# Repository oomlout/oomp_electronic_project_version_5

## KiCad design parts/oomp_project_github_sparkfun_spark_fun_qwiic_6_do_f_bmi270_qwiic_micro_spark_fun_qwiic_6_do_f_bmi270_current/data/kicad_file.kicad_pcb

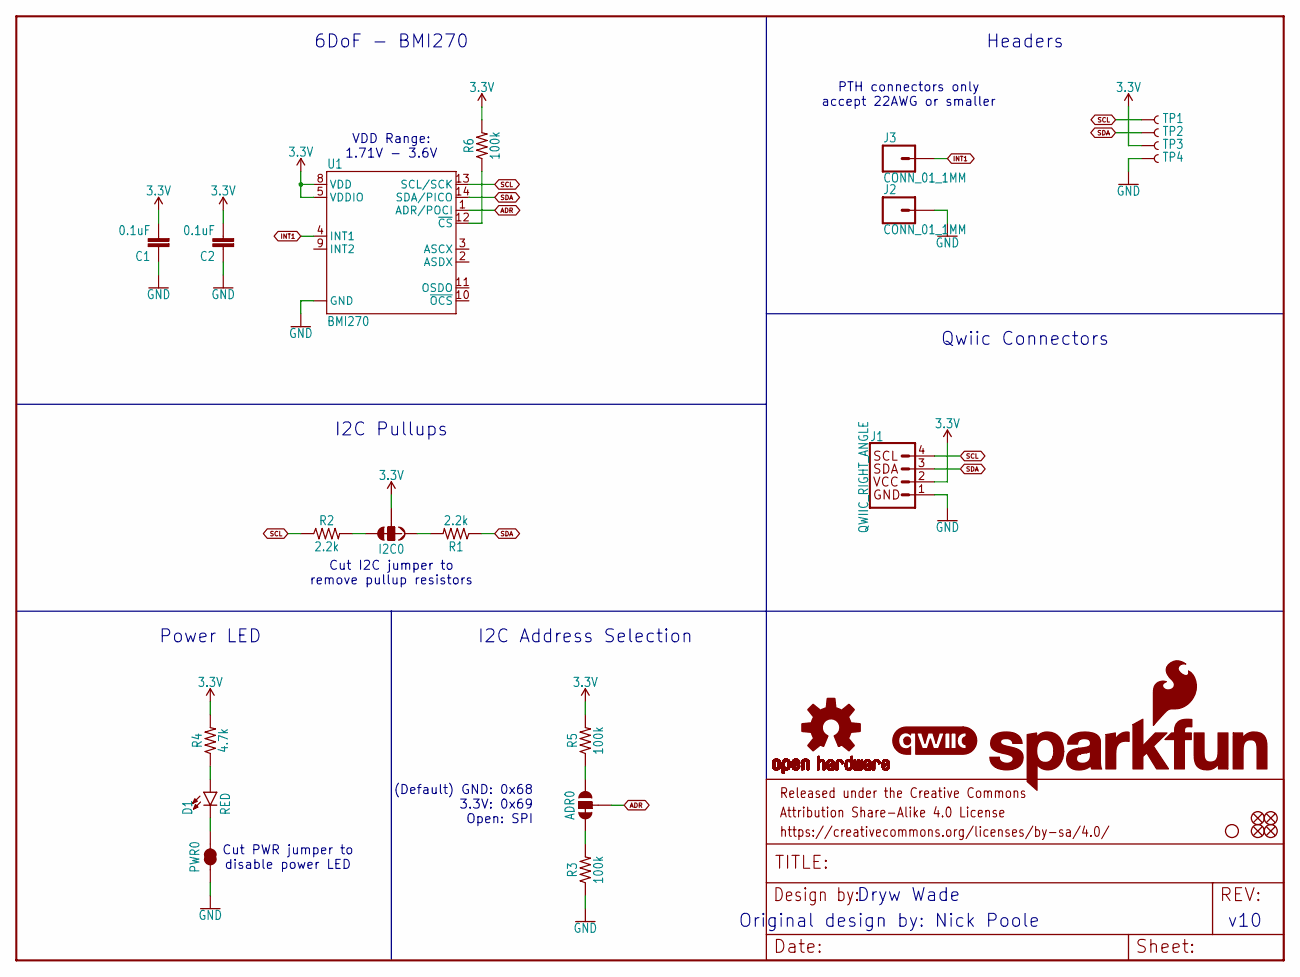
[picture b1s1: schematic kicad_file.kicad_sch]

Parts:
ADR0: JUMPER-SMT_3_1-NC_TRACE_SILK; SMT-JUMPER_3_1-NC_TRACE_SILK
C1, C2: 0.1uF; 0402-TIGHT
D1: RED; LED-0402
FD1, FD2, FD3, FD4: FIDUCIALUFIDUCIAL; FIDUCIAL-MICRO
FRAME1: FRAME-LETTER; CREATIVE_COMMONS
H1: STAND-OFF
I2C0: JUMPER-SMT_3_2-NC_TRACE_SILK; SMT-JUMPER_3_2-NC_TRACE_SILK
J1: QWIIC_RIGHT_ANGLE; JST04_1MM_RA
J2, J3: CONN_01_1MM; 1X01_1MM_NO_SILK
LOGO1: SFE_LOGO_NAME_FLAMEBLANK; BLANK
LOGO2: QWIIC_LOGO_3MM; QWIIC_3MM
LOGO3: OSHW-LOGOMINI; OSHW-LOGO-MINI
PWR0: JUMPER-SMT_2_NC_TRACE_SILK; SMT-JUMPER_2_NC_TRACE_SILK
R1, R2: 2.2k; 0402-TIGHT
R3, R5, R6: 100k; 0402-TIGHT
R4: 4.7k; 0402-TIGHT
TP1, TP2, TP3, TP4: TEST-POINT3; PAD.03X.03
U1: BMI270

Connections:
3.3V: C1.2, C2.2, I2C0.2, J1.2, R4.2, R5.2, R6.2, TP3.1, U1.5 (VDDIO), U1.8 (VDD)
ADR: ADR0.2, U1.1 (ADR/POCI)
GND: C1.1, C2.1, J1.1, J2.1, PWR0.1, R3.1, TP4.1, U1.6 (GND), U1.7 (GND)
INT1: J3.1, U1.4 (INT1)
unnamed: I2C0.1, R1.2
unnamed: I2C0.3, R2.2
unnamed: D1.C, PWR0.2
unnamed: D1.A, R4.1
unnamed: ADR0.1, R5.1
unnamed: ADR0.3, R3.2
unnamed: R6.1, U1.12 (~CS)
SCL: J1.4, R2.1, TP1.1, U1.13 (SCL/SCK)
SDA: J1.3, R1.1, TP2.1, U1.14 (SDA/PICO)

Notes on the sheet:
Qwiic Connectors
Power LED
I2C Pullups
Dryw Wade
v10
Original design by: Nick Poole
Cut I2C jumper to remove pullup resistors
Cut PWR jumper to disable power LED
6DoF - BMI270
I2C Address Selection
Headers
PTH connectors only accept 22AWG or smaller
VDD Range: 1.71V - 3.6V
(Default) GND: 0x68 3.3V: 0x69 Open: SPI

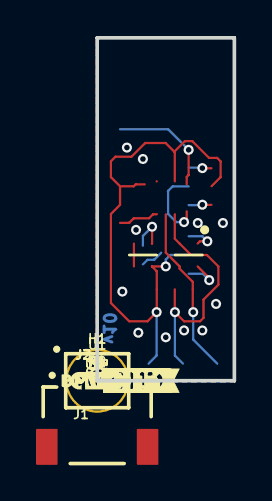
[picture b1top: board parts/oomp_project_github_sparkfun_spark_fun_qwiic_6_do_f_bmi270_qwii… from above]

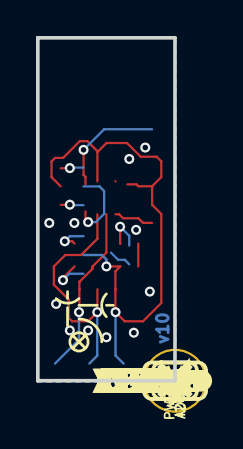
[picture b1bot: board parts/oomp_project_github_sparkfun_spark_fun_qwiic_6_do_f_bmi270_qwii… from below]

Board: 2 copper layers, 7.6 x 19.1 mm, 45 parts (22 on the bottom side), 13 nets.

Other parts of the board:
U$1: #I2C#0
U$2, U$7: #GND#0
U$3: SFE_LOGO_FLAME_.1
U$4: #PWR#0
U$5: #ADR#0
U$6: #0X68#0
U$8, U$9: #INT1#0
U$18: #0X69#0
U$21: BMI2700
U$33: ORDERING_INSTRUCTIONS
U$34: PWR0
U$79: X0
U$80: Y0
U$81: Z0

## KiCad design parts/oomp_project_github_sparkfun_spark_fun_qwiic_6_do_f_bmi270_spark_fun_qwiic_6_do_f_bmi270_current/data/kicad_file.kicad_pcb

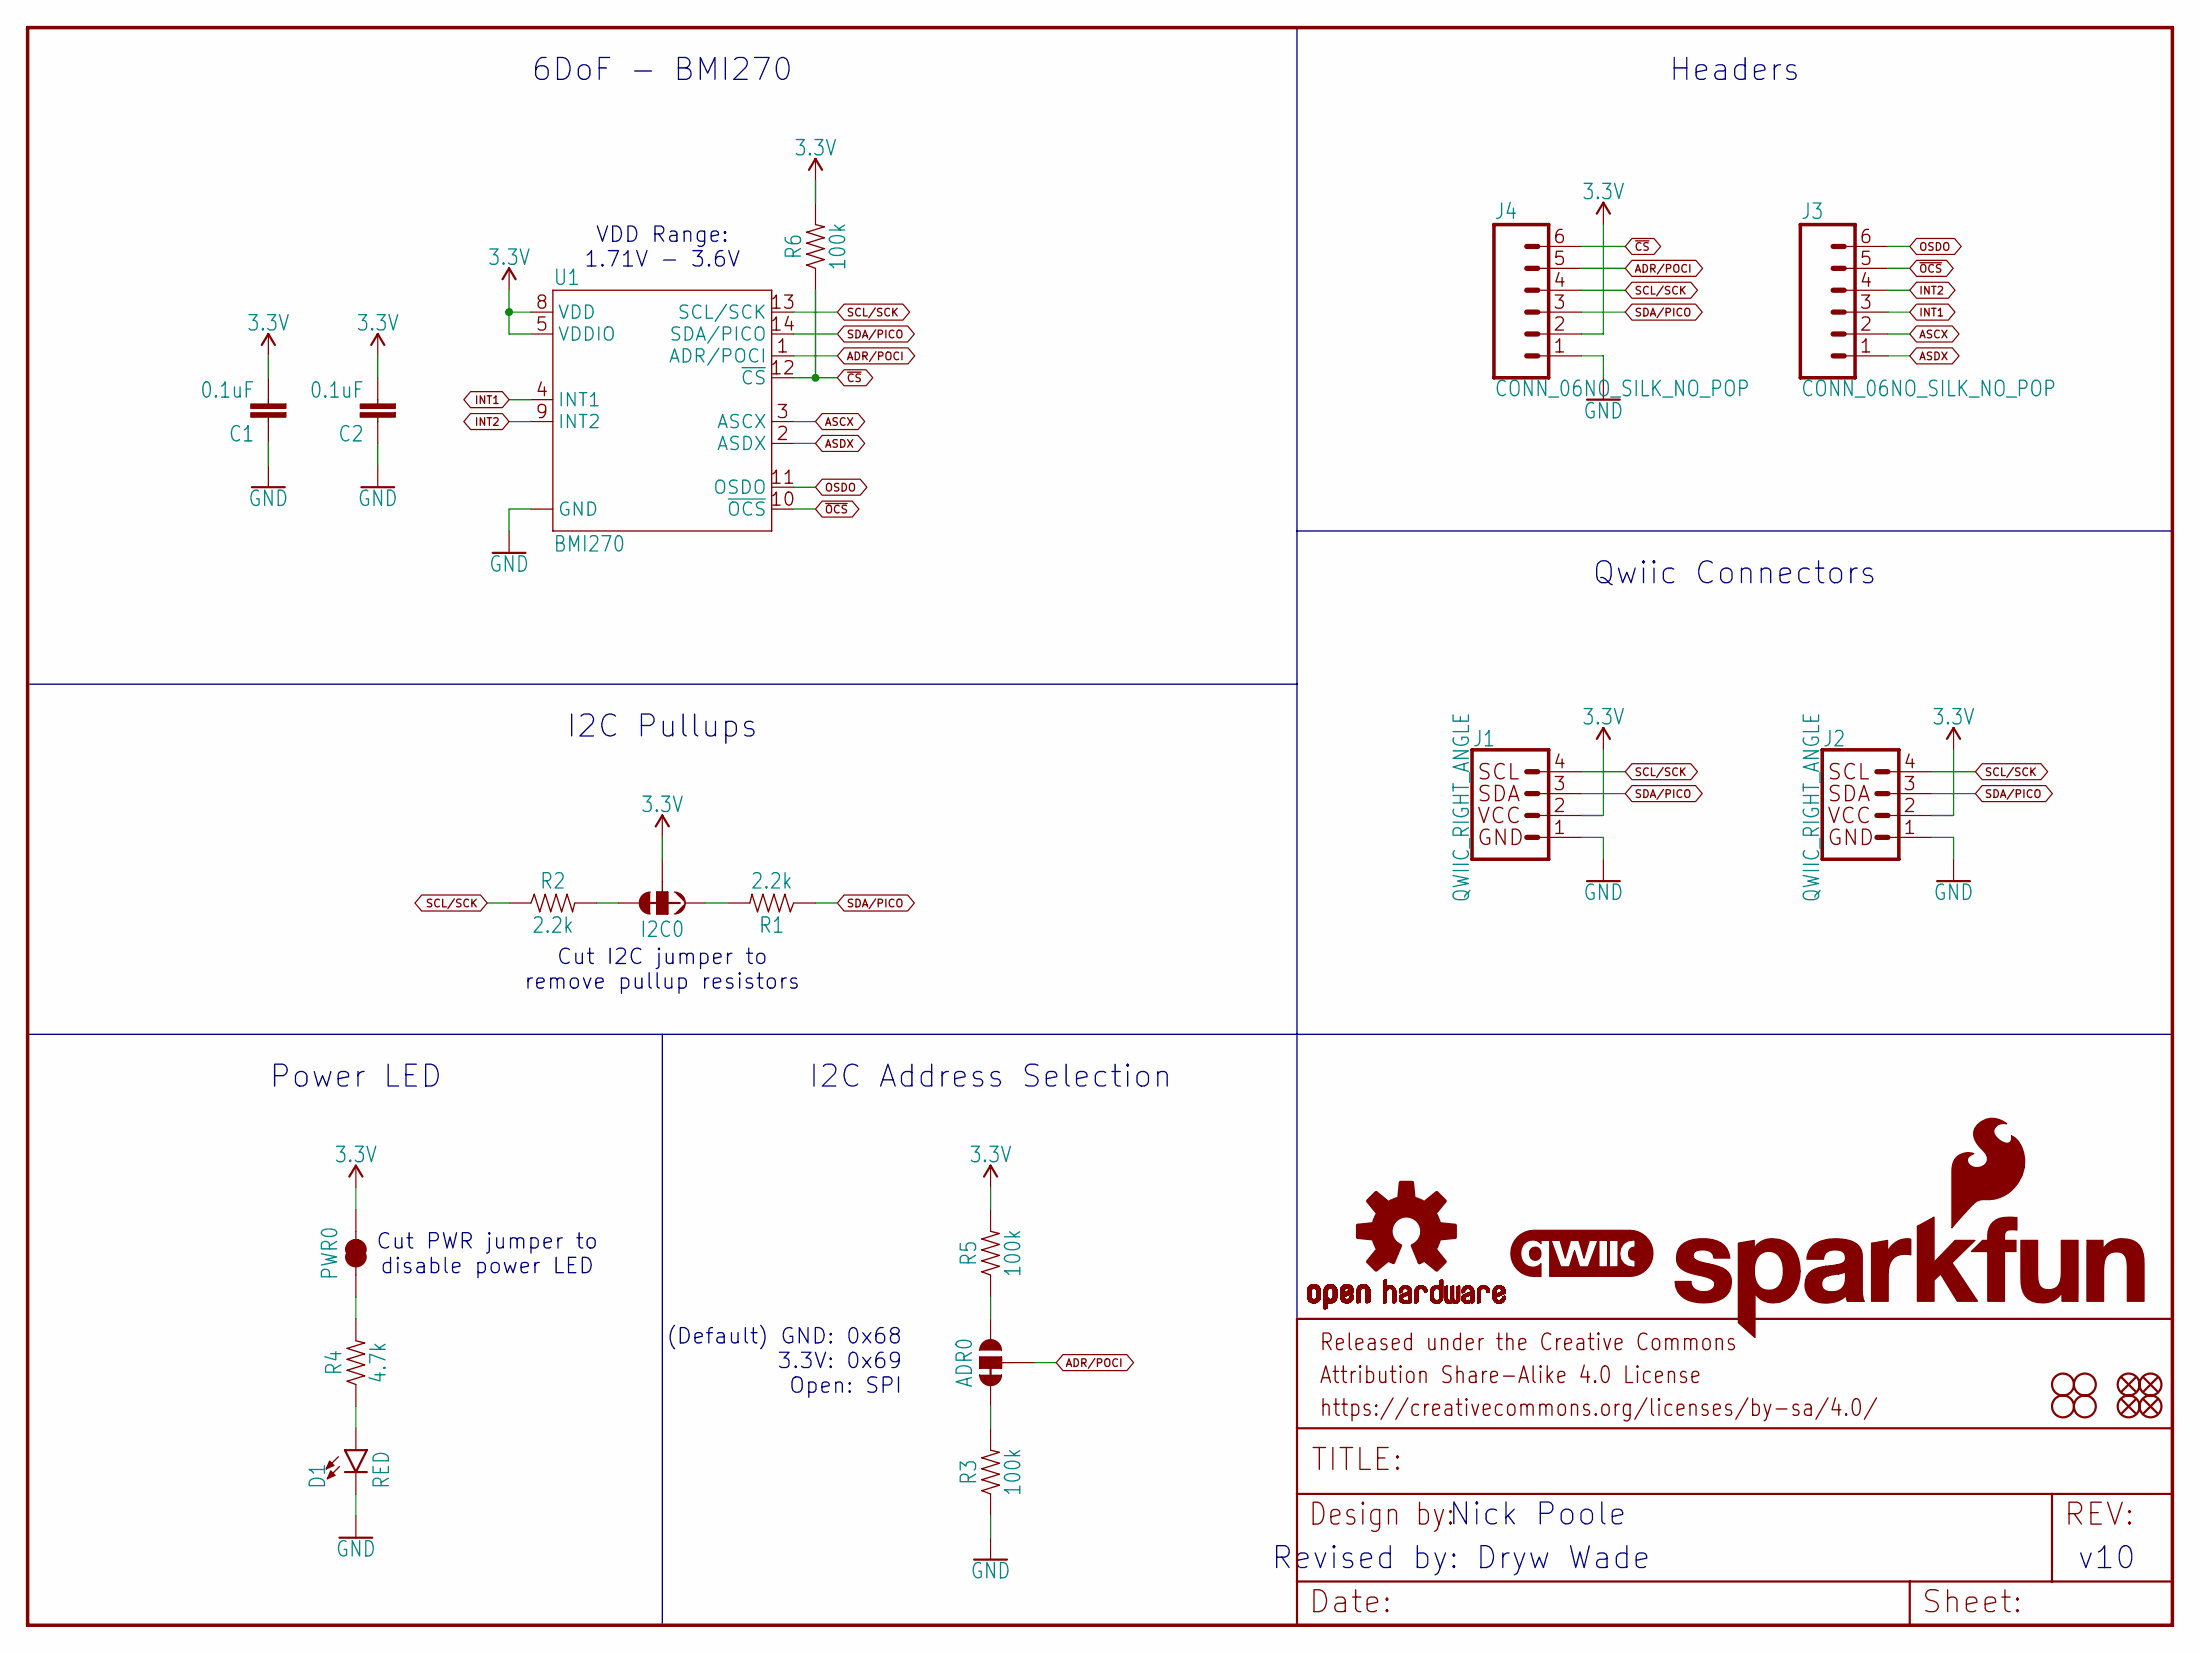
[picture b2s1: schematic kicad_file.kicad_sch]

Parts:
ADR0: JUMPER-SMT_3_1-NC_TRACE_SILK; SMT-JUMPER_3_1-NC_TRACE_SILK
C1, C2: 0.1uF; 0603
D1: RED; LED-0603
FD1, FD2, FD3, FD4: FIDUCIAL1X2; FIDUCIAL-1X2
FRAME1: FRAME-LETTER; CREATIVE_COMMONS
H1, H2, H3, H4: STAND-OFF
I2C0: JUMPER-SMT_3_2-NC_TRACE_SILK; SMT-JUMPER_3_2-NC_TRACE_SILK
J1, J2: QWIIC_RIGHT_ANGLE; JST04_1MM_RA
J3, J4: CONN_06NO_SILK_NO_POP; 1X06_NO_SILK
LOGO1: SFE_LOGO_NAME_FLAME.1_INCH; SFE_LOGO_NAME_FLAME_.1
LOGO2: QWIIC_LOGO_5MM; QWIIC_5MM
LOGO3: OSHW-LOGOS; OSHW-LOGO-S
PWR0: JUMPER-SMT_2_NC_TRACE_SILK; SMT-JUMPER_2_NC_TRACE_SILK
R1, R2: 2.2k; 0603
R3, R5, R6: 100k; 0603
R4: 4.7k; 0603
U1: BMI270

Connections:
3.3V: C1.2, C2.2, I2C0.2, J1.2, J2.2, J4.2, PWR0.2, R5.2, R6.2, U1.5 (VDDIO), U1.8 (VDD)
ADR/POCI: ADR0.2, J4.5, U1.1 (ADR/POCI)
ASCX: J3.2, U1.3 (ASCX)
ASDX: J3.1, U1.2 (ASDX)
GND: C1.1, C2.1, D1.C, J1.1, J2.1, J4.1, R3.1, U1.6 (GND), U1.7 (GND)
INT1: J3.3, U1.4 (INT1)
INT2: J3.4, U1.9 (INT2)
unnamed: I2C0.1, R1.2
unnamed: I2C0.3, R2.2
unnamed: PWR0.1, R4.2
unnamed: D1.A, R4.1
unnamed: ADR0.1, R5.1
unnamed: ADR0.3, R3.2
OSDO: J3.6, U1.11 (OSDO)
SCL/SCK: J1.4, J2.4, J4.4, R2.1, U1.13 (SCL/SCK)
SDA/PICO: J1.3, J2.3, J4.3, R1.1, U1.14 (SDA/PICO)
~CS: J4.6, R6.1, U1.12 (~CS)
~OCS: J3.5, U1.10 (~OCS)

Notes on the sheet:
Headers
(Default) GND: 0x68 3.3V: 0x69 Open: SPI
Revised by: Dryw Wade
v10
I2C Address Selection
VDD Range: 1.71V - 3.6V
I2C Pullups
Qwiic Connectors
Cut PWR jumper to disable power LED
Nick Poole
Cut I2C jumper to remove pullup resistors
6DoF - BMI270
Power LED

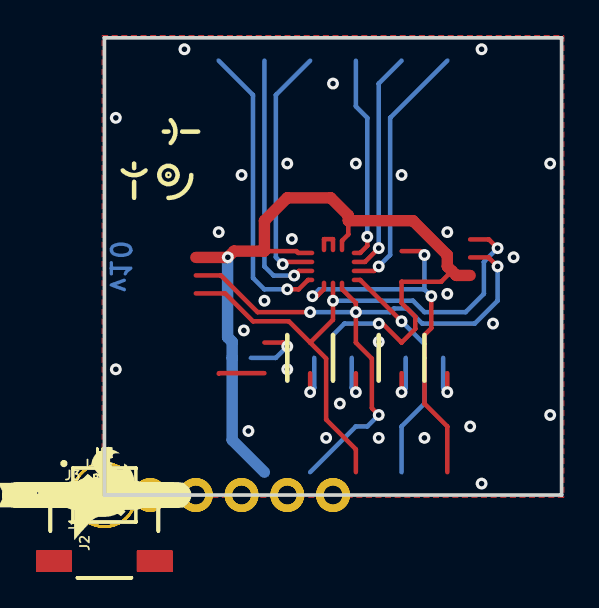
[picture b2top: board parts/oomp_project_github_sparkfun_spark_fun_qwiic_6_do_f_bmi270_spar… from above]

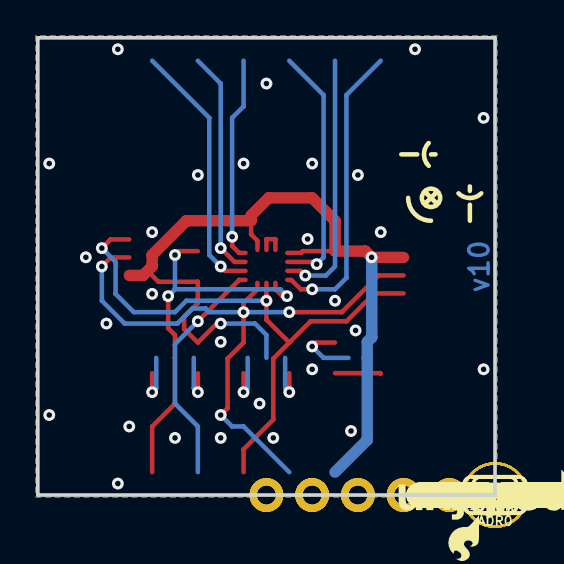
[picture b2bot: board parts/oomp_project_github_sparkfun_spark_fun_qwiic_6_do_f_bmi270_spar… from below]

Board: 2 copper layers, 25.4 x 25.4 mm, 69 parts (27 on the bottom side), 18 nets.

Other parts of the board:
U$1: #I2C#0
U$2, U$14: #_SDA#0
U$3: SFE_LOGO_FLAME_.2
U$4: #PWR#0
U$5: #ADR#0
U$6: #0X68#0
U$7, U$13: #_3V3#0
U$8, U$17: #_#CS##0
U$9, U$16: #_ADR#0
U$10, U$15: #_SCL#0
U$11, U$27: #ASDX_#0
U$12, U$19: #_GND#0
U$18: #0X69#0
U$20, U$21: BMI2700
U$22, U$28: #ASCX_#0
U$23, U$29: #INT1_#0
U$24, U$30: #INT2_#0
U$25, U$31: ##OCS#_#0
U$26, U$32: #OSDO_#0
U$33: ORDERING_INSTRUCTIONS
U$34: PWR0
U$79, U$88: X0
U$80, U$89: Y0
U$81, U$90: Z0

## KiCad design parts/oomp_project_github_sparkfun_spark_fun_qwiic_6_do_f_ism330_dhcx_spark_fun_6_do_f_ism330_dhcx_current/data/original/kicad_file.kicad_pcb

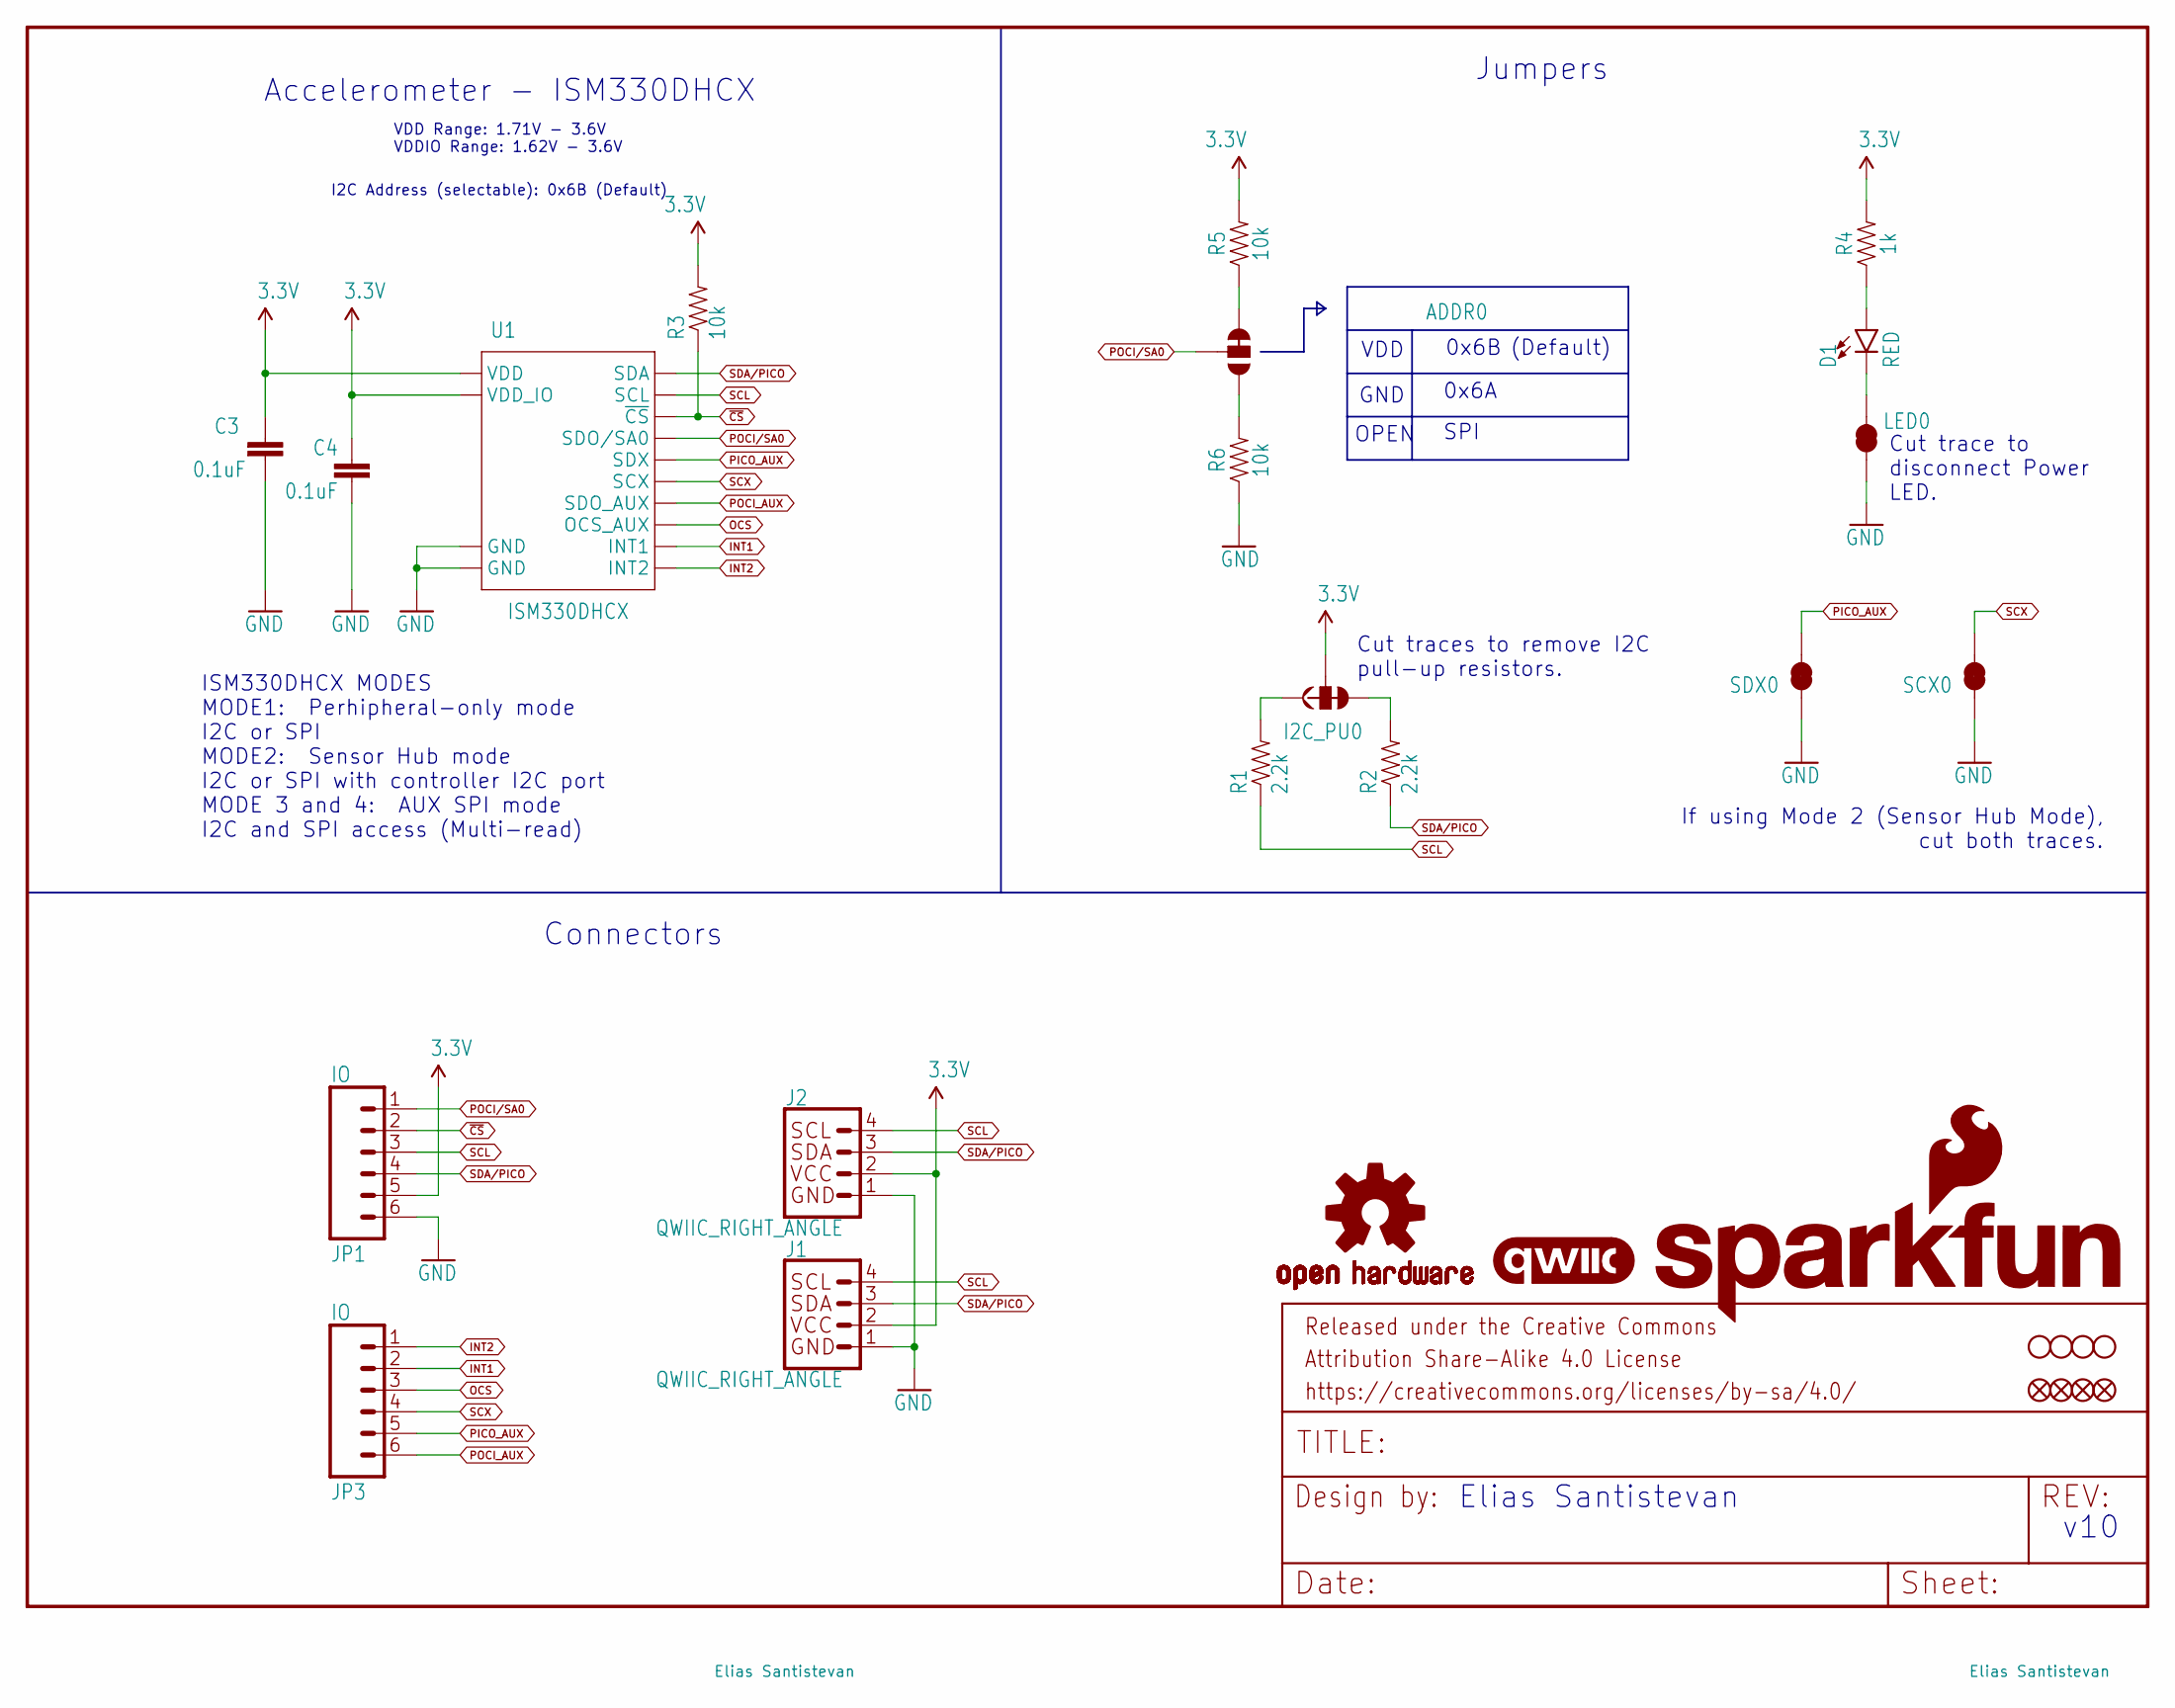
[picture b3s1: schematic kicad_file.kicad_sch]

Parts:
ADDR0: JUMPER-SMT_3_1-NC_TRACE_SILK; SMT-JUMPER_3_1-NC_TRACE_SILK
C3, C4: 0.1uF; 0603
D1: RED; LED-0603
FD1, FD2: FIDUCIALUFIDUCIAL; FIDUCIAL-MICRO
FID1, FID2: FIDUCIALUFIDUCIAL; FIDUCIAL-MICRO
FRAME1: FRAME-LETTER; CREATIVE_COMMONS
I2C_PU0: S_MODE; SMT-JUMPER_3_2-NC_TRACE_SILK
J1, J2: QWIIC_RIGHT_ANGLE; JST04_1MM_RA
JP1, JP3: IO; 1X06_NO_SILK
LED0: JUMPER-SMT_2_NC_TRACE_SILK; SMT-JUMPER_2_NC_TRACE_SILK
LOGO1: QWIIC_LOGO_4MM; QWIIC_4MM
LOGO2: OSHW-LOGOMINI; OSHW-LOGO-MINI
LOGO3: SFE_LOGO_NAME_FLAME.1_INCH; SFE_LOGO_NAME_FLAME_.1
R1, R2: 2.2k; 0603
R3, R5, R6: 10k; 0603
R4: 1k; 0603
SCX0: JUMPER-SMT_2_NC_TRACE_SILK; SMT-JUMPER_2_NC_TRACE_SILK
SDX0: JUMPER-SMT_2_NC_TRACE_SILK; SMT-JUMPER_2_NC_TRACE_SILK
STANDOFF1, STANDOFF2, STANDOFF3, STANDOFF4: STAND-OFFTIGHT; STAND-OFF-TIGHT
U1: ISM330DHCX; LGA-14L

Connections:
3.3V: C3.1, C4.1, I2C_PU0.2, J1.2, J2.2, JP1.5, R3.2, R4.2, R5.2, U1.P5 (VDD_IO), U1.P8 (VDD)
GND: C3.2, C4.2, J1.1, J2.1, JP1.6, LED0.1, R6.1, SCX0.1, SDX0.1, U1.P6 (GND), U1.P7 (GND)
INT1: JP3.2, U1.P4 (INT1)
INT2: JP3.1, U1.P9 (INT2)
unnamed: ADDR0.3, R5.1
unnamed: D1.A, R4.1
unnamed: D1.C, LED0.2
unnamed: I2C_PU0.1, R1.2
unnamed: I2C_PU0.3, R2.2
unnamed: ADDR0.1, R6.2
OCS: JP3.3, U1.P10 (OCS_AUX)
PICO_AUX: JP3.5, SDX0.2, U1.P2 (SDX)
POCI/SA0: ADDR0.2, JP1.1, U1.P1 (SDO/SA0)
POCI_AUX: JP3.6, U1.P11 (SDO_AUX)
SCL: J1.4, J2.4, JP1.3, R1.1, U1.P13 (SCL)
SCX: JP3.4, SCX0.2, U1.P3 (SCX)
SDA/PICO: J1.3, J2.3, JP1.4, R2.1, U1.P14 (SDA)
~CS: JP1.2, R3.1, U1.P12 (~CS)

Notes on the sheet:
I2C Address (selectable): 0x6B (Default)
SPI
Jumpers
Cut trace to disconnect Power LED.
0x6B
If using Mode 2 (Sensor Hub Mode), cut both traces.
Accelerometer - ISM330DHCX
GND
Connectors
Elias Santistevan
0x6A
Cut traces to remove I2C pull-up resistors.
VDD Range: 1.71V - 3.6V VDDIO Range: 1.62V - 3.6V
VDD
OPEN
v10
ISM330DHCX MODES MODE1: Perhipheral-only mode I2C or SPI MODE2: Sensor Hub mode I2C or SPI with controller I2C port MODE 3 and 4: AUX SPI mode I2C and SPI access (Multi-read)
(Default)

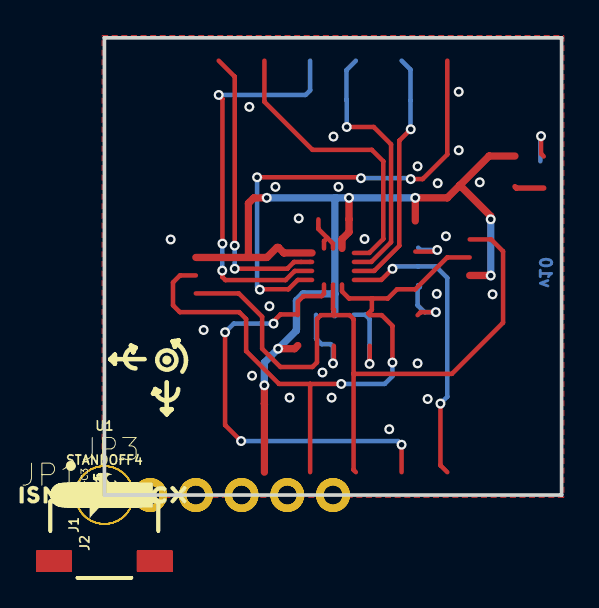
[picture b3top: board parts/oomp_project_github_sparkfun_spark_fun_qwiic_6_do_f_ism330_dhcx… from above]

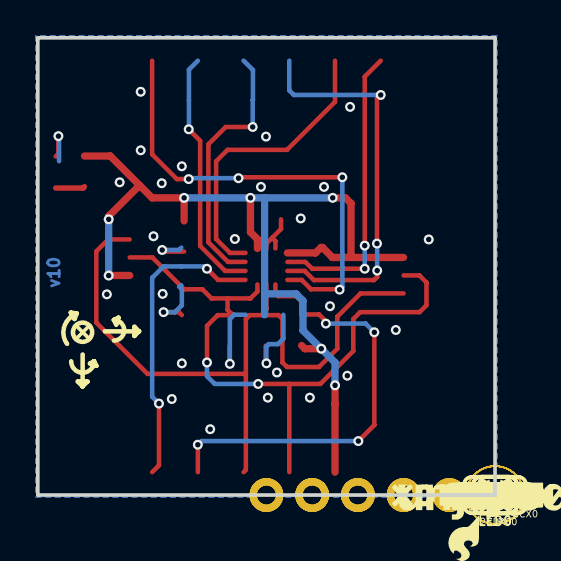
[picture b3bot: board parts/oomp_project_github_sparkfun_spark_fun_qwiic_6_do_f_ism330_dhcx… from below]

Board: 2 copper layers, 25.4 x 25.4 mm, 70 parts (30 on the bottom side), 18 nets.

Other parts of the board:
U$1, U$15: #3V3#1
U$2, U$17: #GND#0
U$3: ##CS##7
U$4: #SDA#4
U$5, U$22: #SCL#5
U$6: #POCI#11
U$7, U$19: #INT1#9
U$8: #INT2#2
U$9: #OCS#8
U$10: #SCX#9
U$11: #PICOX#10
U$12: ISM330DHCX331
U$13: #0X6A#11
U$14: #0X6B#11
U$16: #LED#11
U$18: #POCI#12
U$20: #OCS#7
U$23: #SCX#8
U$24: #POCIX#8
U$25: #I2C#11
U$26: #PICO#13
U$27: ##CS##8
U$28: PWR8
U$29: SFE_LOGO_FLAME_.1
U$30: ISM330DHCX20
U$31: 6DOF12
U$32: #PICOX#9
U$33: #POCIX#7
U$34, U$37: X2114
U$35, U$38: Y2115
U$36, U$39: Z2116
U$40: #INT2#3

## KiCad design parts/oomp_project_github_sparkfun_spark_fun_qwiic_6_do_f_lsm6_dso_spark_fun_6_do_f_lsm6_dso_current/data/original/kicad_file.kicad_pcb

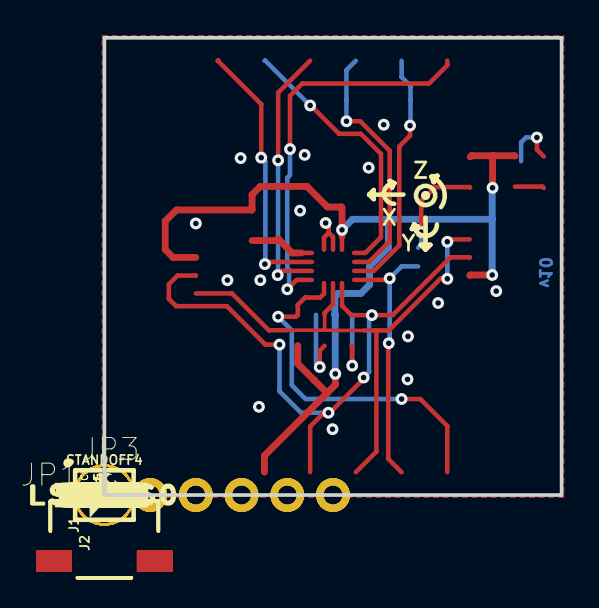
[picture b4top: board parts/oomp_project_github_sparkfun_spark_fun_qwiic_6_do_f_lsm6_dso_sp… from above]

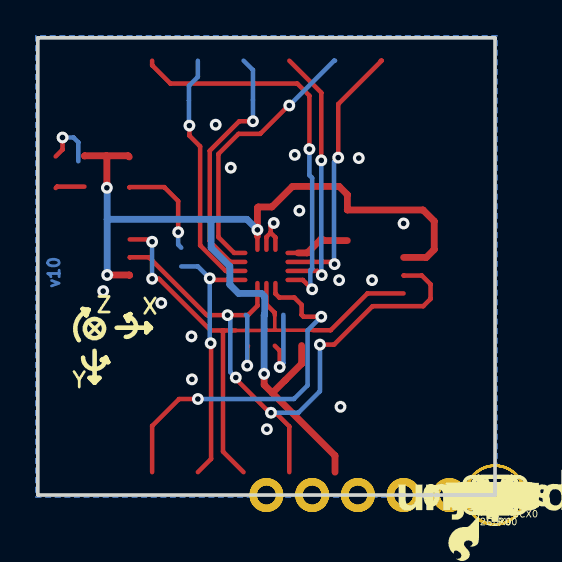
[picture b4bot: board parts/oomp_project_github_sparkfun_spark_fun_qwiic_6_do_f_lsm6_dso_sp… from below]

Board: 2 copper layers, 25.4 x 25.4 mm, 64 parts (27 on the bottom side), 18 nets.

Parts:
ADDR0: JUMPER-SMT_3_1-NC_TRACE_SILK; SMT-JUMPER_3_1-NC_TRACE_SILK
C3, C4: 0.1uF; 0603
D1: RED; LED-0603
FD1, FD2: FIDUCIALUFIDUCIAL; FIDUCIAL-MICRO
FID1, FID2: FIDUCIALUFIDUCIAL; FIDUCIAL-MICRO
FRAME1: FRAME-LETTER; CREATIVE_COMMONS
I2C_PU0: S_MODE; SMT-JUMPER_3_2-NC_TRACE_SILK
J1, J2: QWIIC_RIGHT_ANGLE; JST04_1MM_RA
JP1, JP3: IO; 1X06_NO_SILK
L1: 30Ω; 0603
LED0: JUMPER-SMT_2_NC_TRACE_SILK; SMT-JUMPER_2_NC_TRACE_SILK
LOGO1: QWIIC_LOGO_4MM; QWIIC_4MM
LOGO2: OSHW-LOGOS; OSHW-LOGO-S
LOGO3: SFE_LOGO_NAME_FLAME.1_INCH; SFE_LOGO_NAME_FLAME_.1
R1, R2: 4.7k; 0603
R3: 10k; 0603
R4: 1k; 0603
R5: 100k; 0603
SCX0: JUMPER-SMT_2_NC_TRACE_SILK; SMT-JUMPER_2_NC_TRACE_SILK
SDX0: JUMPER-SMT_2_NC_TRACE_SILK; SMT-JUMPER_2_NC_TRACE_SILK
STANDOFF1, STANDOFF2, STANDOFF3, STANDOFF4: STAND-OFFTIGHT; STAND-OFF-TIGHT
U1: LSM6DS0; LGA14L
U$1, U$15: #3V3#1
U$2, U$17: #GND#0
U$3: ##CS##7
U$4: #SDA#4
U$5, U$22: #SCL#5
U$6: #SDO#6
U$7, U$19: #INT1#9
U$8, U$21: #INT2#9
U$9: #OCS#8
U$10: #SCX#9
U$11, U$33: #SDIX#11
U$12, U$30: LSM6DS011
U$13: #0X6A#11
U$14: #0X6B#11
U$16: #LED#11
U$18: #SDO#7
U$20: #OCS#7
U$23: #SCX#8
U$24, U$32: #SDOX#12
U$25: #I2C#11
U$26: #SDI#4
U$27: ##CS##8
U$28: PWR8
U$29: SFE_LOGO_FLAME_.1
U$31: 6DOF12

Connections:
3.3V: C4.1, I2C_PU0.2, J1.2, J2.2, JP1.5, L1.1, R3.2, R4.2, R5.2, U1.5
GND: ADDR0.1, C3.2, C4.2, J1.1, J2.1, JP1.6, LED0.1, SCX0.1, SDX0.1, U1.6, U1.7
INT1: JP3.2, U1.4
INT2: JP3.1, U1.9
unnamed: ADDR0.3, R5.1
unnamed: D1.A, R4.1
unnamed: D1.C, LED0.2
unnamed: I2C_PU0.1, R1.2
unnamed: I2C_PU0.3, R2.2
OCS: JP3.3, U1.10
SCL: J1.4, J2.4, JP1.3, R1.1, U1.13
SCX: JP3.4, SCX0.2, U1.3
SDA: J1.3, J2.3, JP1.4, R2.1, U1.14
SDI_AUX: JP3.5, SDX0.2, U1.2
SDO/SA0: ADDR0.2, JP1.2, U1.1
SDO_AUX: JP3.6, U1.11
VDD: C3.1, L1.2, U1.8
~CS: JP1.1, R3.1, U1.12

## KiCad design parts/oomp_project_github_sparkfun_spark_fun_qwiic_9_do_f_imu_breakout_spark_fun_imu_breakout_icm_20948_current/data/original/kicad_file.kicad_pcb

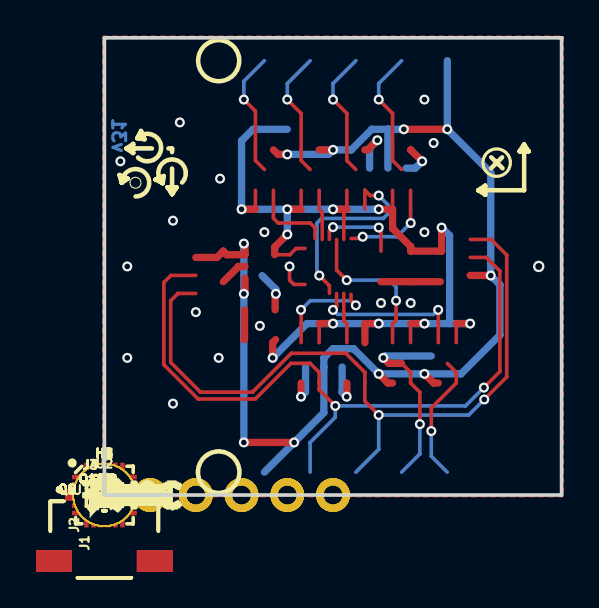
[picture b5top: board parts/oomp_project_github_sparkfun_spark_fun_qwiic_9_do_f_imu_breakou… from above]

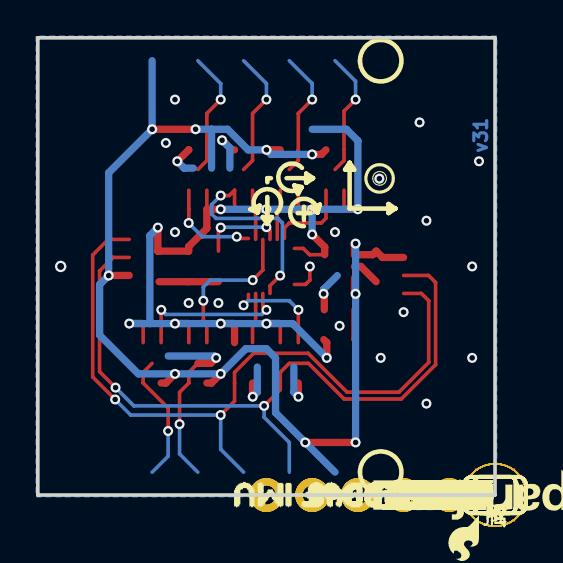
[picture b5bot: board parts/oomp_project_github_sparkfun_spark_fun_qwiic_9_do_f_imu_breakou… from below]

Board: 2 copper layers, 25.4 x 25.4 mm, 104 parts (36 on the bottom side), 26 nets.

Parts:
C1, C4: 1.0uF; 0603
C2, C3: 0.1uF; 0603
D1: RED; LED-0603
FD1, FD2, FD3, FD4: FIDUCIAL1X2; FIDUCIAL-1X2
FRAME2: FRAME-LEDGER; CREATIVE_COMMONS
H1, H2, H3, H4: STAND-OFF
J1, J2: JST04_1MM_RA
J3, J4: 1X06_NO_SILK
JP2: ADR; SMT-JUMPER_2_NO_SILK
JP3: AUX; SMT-JUMPER_3_2-NC_TRACE_SILK
JP4: I2C PU; SMT-JUMPER_3_2-NC_TRACE_SILK
JP5: LED; SMT-JUMPER_2_NC_TRACE_SILK
LOGO1: SFE_LOGO_NAME_FLAME.1_INCH; SFE_LOGO_NAME_FLAME_.1
LOGO2: OSHW-LOGOMINI; OSHW-LOGO-MINI
Q2, Q4, Q6, Q8, Q10, Q12, Q14, Q16: 20V/0.2A/8MHz/1.2Ω/1Vth; SOT-416FL
R9: 220; 0603
R10, R11, R12, R13, R14, R15, R16, R17, R18, R19, R20, R21, R22, R23, R24, R25: 2.2k; 0402-TIGHT
TP1: 1.8V; PAD.03X.03
U2: 9DoF IMU; QFN24-3X3
U3: 1.8V/100mA; SC70
U$1, U$2, U$22, U$24: GND4
U$3: PWR0
U$4, U$21: INT3
U$5, U$20: FSNC2
U$6, U$19: ACL1
U$7, U$18: ADA0
U$8: MISO13
U$9: MOSI14
U$10: SCLK15
U$11: #CS16
U$12: 1V8#5V57
U$13, U$30, U$44: VIN5
U$14: NC17
U$15: CL4
U$16: DA2
U$17: AD012
U$23: ADR2
U$25: I2C_PU21
U$26: SPI19
U$27: AUX_PU24
U$28: SFE_LOGO_FLAME_.1
U$29: LED23
U$31: ICM#2094820
U$34, U$40, U$50, U$57: X0
U$35, U$41, U$51, U$58: Y1
U$36, U$42, U$52, U$59: Z2
U$37, U$60: G5
U$38, U$61: A4
U$39, U$49: M3
U$43: QWIIC_9DOF_IMU_0
U$45: I#C1

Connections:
1.8V: C1.1, C2.1, D1.A, Q2.1, Q4.1, Q6.1, Q8.1, Q10.1, Q12.1, Q14.1, Q16.1, R10.2, R12.2, R14.2, R16.2, R18.2, R20.2, R22.2, R24.2, TP1.P$1, U2.8, U2.13, U3.5
AD0/SDO: Q4.2, R12.1, U2.9
AD0/SDO_VIN: J3.5, JP2.2, Q4.3, R13.1
AUX_CL: Q12.2, R20.1, U2.7
AUX_CL_VIN: J4.5, Q12.3, R21.1
AUX_DA: Q10.2, R18.1, U2.21
AUX_DA_VIN: J4.4, Q10.3, R19.1
FSYNC: Q14.2, R22.1, U2.11
FSYNC_VIN: J4.3, Q14.3, R23.1
GND: C1.2, C2.2, C3.2, C4.2, J1.1, J2.1, J3.1, J4.1, JP2.1, JP5.1, U2.18, U2.20, U3.2
INT: Q16.2, R24.1, U2.12
INT_VIN: J4.2, Q16.3, R25.1
unnamed: C3.1, U2.10
unnamed: JP4.3, R15.2
unnamed: JP4.1, R17.2
unnamed: JP3.1, R21.2
unnamed: JP3.3, R19.2
unnamed: D1.C, R9.2
unnamed: JP5.2, R9.1
SCL/SCLK: Q6.2, R14.1, U2.23
SCL/SCLK_VIN: J1.4, J2.4, J3.4, Q6.3, R15.1
SDA/SDI: Q8.2, R16.1, U2.24
SDA/SDI_VIN: J1.3, J2.3, J3.3, Q8.3, R17.1
VIN: C4.1, J1.2, J2.2, J3.2, J4.6, JP3.2, JP4.2, R11.2, R13.2, R23.2, R25.2, U3.1, U3.3
~CS: Q2.2, R10.1, U2.22
~CS_VIN: J3.6, Q2.3, R11.1

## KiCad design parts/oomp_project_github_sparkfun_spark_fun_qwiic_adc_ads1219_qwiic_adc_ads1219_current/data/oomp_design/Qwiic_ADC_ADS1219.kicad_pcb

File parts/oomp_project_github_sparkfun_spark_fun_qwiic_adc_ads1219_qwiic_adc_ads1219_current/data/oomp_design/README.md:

# OOMP KiCad design copy

Open `Qwiic_ADC_ADS1219.kicad_pro` (or the `.kicad_pcb` / `.kicad_sch`) in KiCad. Local OOMP libraries are under `libraries/`. Original inputs are preserved in [../original/](../original/).

Only verified unchanged installed KiCad defaults were renamed. Modified, custom, unmatched and unavailable items remain unchanged. Soldering variants are never swapped during conversion. Existing pad coordinates, nets and UUIDs are preserved.

See [conversion_report.yaml](conversion_report.yaml) for every conversion and skip. Copy this directory before editing; regeneration refuses to overwrite edited design files.

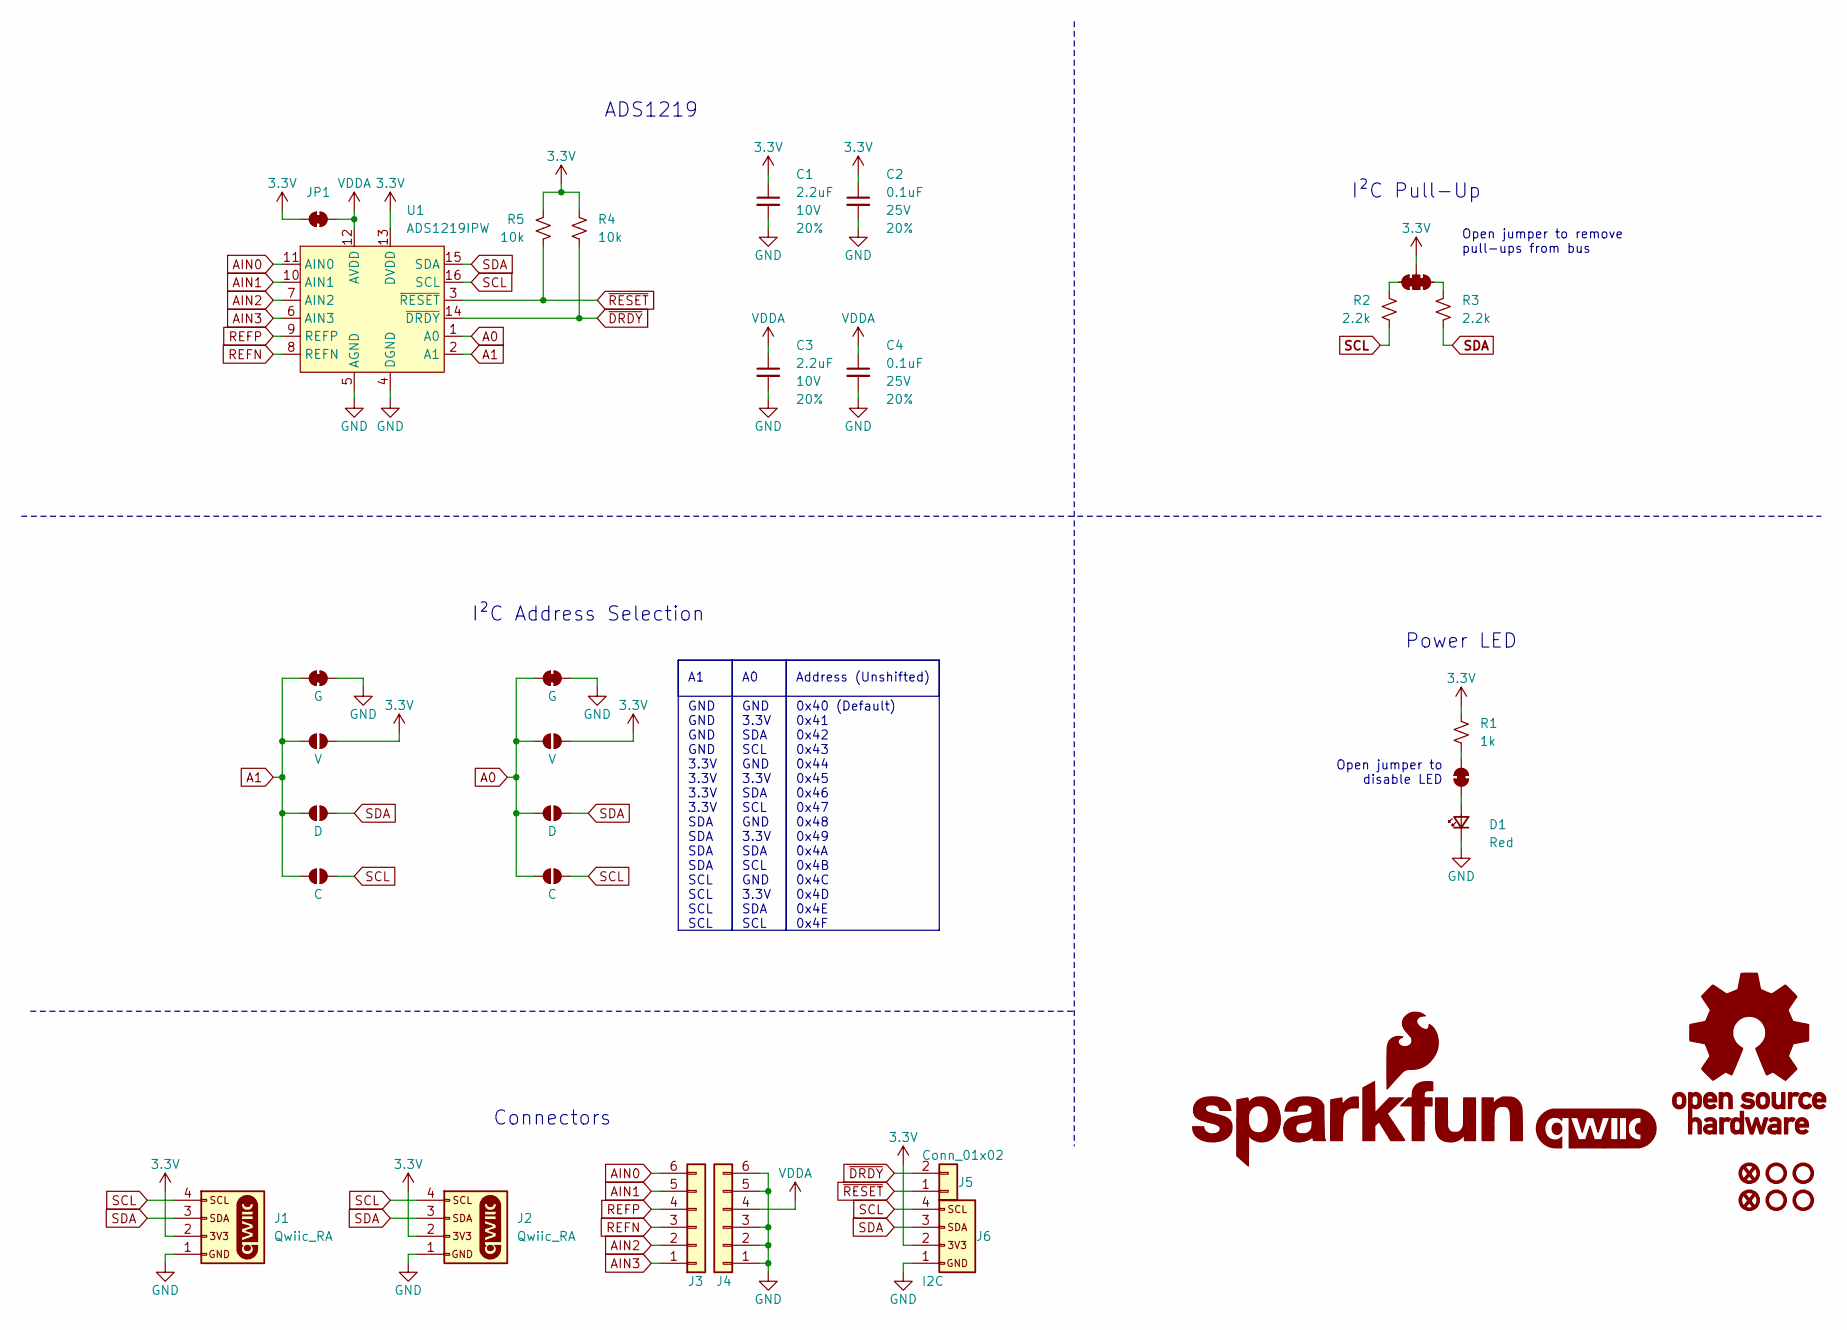
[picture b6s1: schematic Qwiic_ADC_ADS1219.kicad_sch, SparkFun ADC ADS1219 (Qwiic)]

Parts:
C1, C3: 2.2uF; C_0603_1608Metric; Voltage 10V; Tolerance 20%
C2, C4: 0.1uF; C_0603_1608Metric; Voltage 25V; Tolerance 20%
D1: Red; LED_0603_1608Metric_Red
FID1, FID3: Fiducial_0.5mm; Fiducial_0.5mm_Mask1mm
G1: SparkFun_Logo
J1, J2: Qwiic_RA; JST_SMD_1.0mm-4_Black
J3, J4: Conn_01x06; 1x06
J5: Conn_01x02; 1x02
J6: I2C; 1x04
JP1, JP2: Jumper_2_NC_Trace
JP3: Jumper_3_NC-2_Trace
JP4, JP8: G; Jumper_2_NC_Trace
JP5, JP9: V; Jumper_2_NO
JP6, JP10: D; Jumper_2_NO
JP7, JP11: C; Jumper_2_NO
R1: 1k; R_0603_1608Metric
R2, R3: 2.2k; R_0603_1608Metric
R4, R5: 10k; R_0603_1608Metric
ST1, ST2, ST3, ST4: Standoff
U1: ADS1219IPW; TSSOP-16

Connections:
3.3V: C1.1, C2.1, J1.2, J2.2, J6.2, JP1.1 (A), JP3.2 (B), JP5.2 (B), JP9.2 (B), R1.2, R4.2, R5.1, U1.13 (DVDD)
A0: JP4.1 (A), JP5.1 (A), JP6.1 (A), JP7.1 (A), U1.1 (A0)
A1: JP8.1 (A), JP9.1 (A), JP10.1 (A), JP11.1 (A), U1.2 (A1)
AIN0: J3.6, U1.11 (AIN0)
AIN1: J3.5, U1.10 (AIN1)
AIN2: J3.2, U1.7 (AIN2)
AIN3: J3.1, U1.6 (AIN3)
GND: C1.2, C2.2, C3.2, C4.2, D1.1 (K), J1.1, J2.1, J4.1, J4.2, J4.3, J4.5, J4.6, J6.1, JP4.2 (B), JP8.2 (B), U1.4 (DGND), U1.5 (AGND)
unnamed: D1.2 (A), JP2.1 (A)
unnamed: JP2.2 (B), R1.1
unnamed: JP3.1 (A), R3.1
unnamed: JP3.3 (C), R2.2
REFN: J3.3, U1.8 (REFN)
REFP: J3.4, U1.9 (REFP)
SCL: J1.4, J2.4, J6.4, JP7.2 (B), JP11.2 (B), R2.1, U1.16 (SCL)
SDA: J1.3, J2.3, J6.3, JP6.2 (B), JP10.2 (B), R3.2, U1.15 (SDA)
VDDA: C3.1, C4.1, J4.4, JP1.2 (B), U1.12 (AVDD)
~DRDY: J5.2, R4.1, U1.14 (~DRDY)
~RESET: J5.1, R5.2, U1.3 (~RESET)

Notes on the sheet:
Open jumper to remove pull-ups from bus
Connectors
Power LED
I²C Address Selection
Open jumper to disable LED
A1 GND GND GND GND 3.3V 3.3V 3.3V 3.3V SDA SDA SDA SDA SCL SCL SCL SCL
Address (Unshifted) 0x40 (Default) 0x41 0x42 0x43 0x44 0x45 0x46 0x47 0x48 0x49 0x4A 0x4B 0x4C 0x4D 0x4E 0x4F
ADS1219
I²C Pull-Up
A0 GND 3.3V SDA SCL GND 3.3V SDA SCL GND 3.3V SDA SCL GND 3.3V SDA SCL

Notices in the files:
parts/oomp_project_github_sparkfun_spark_fun_qwiic_6_do_f_bmi270_qwiic_micro_spark_fun_qwiic_6_do_f_bmi270_current/data/kicad_file.kicad_sch:
Released under the Creative Commons
https://creativecommons.org/licenses/by-sa/4.0
parts and their libraries:
Released under the Creative Commons Attribution Share-Alike 4.0 License
